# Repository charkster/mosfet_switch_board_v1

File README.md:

MOSFET Switch board which can quickly toggle the switch and then toggle GPIO pins by a programmable delay.

An Adafruit QT PY SAMD21 UF2 file is included. See test_mosfet_switch_board.py for SCPI commands.

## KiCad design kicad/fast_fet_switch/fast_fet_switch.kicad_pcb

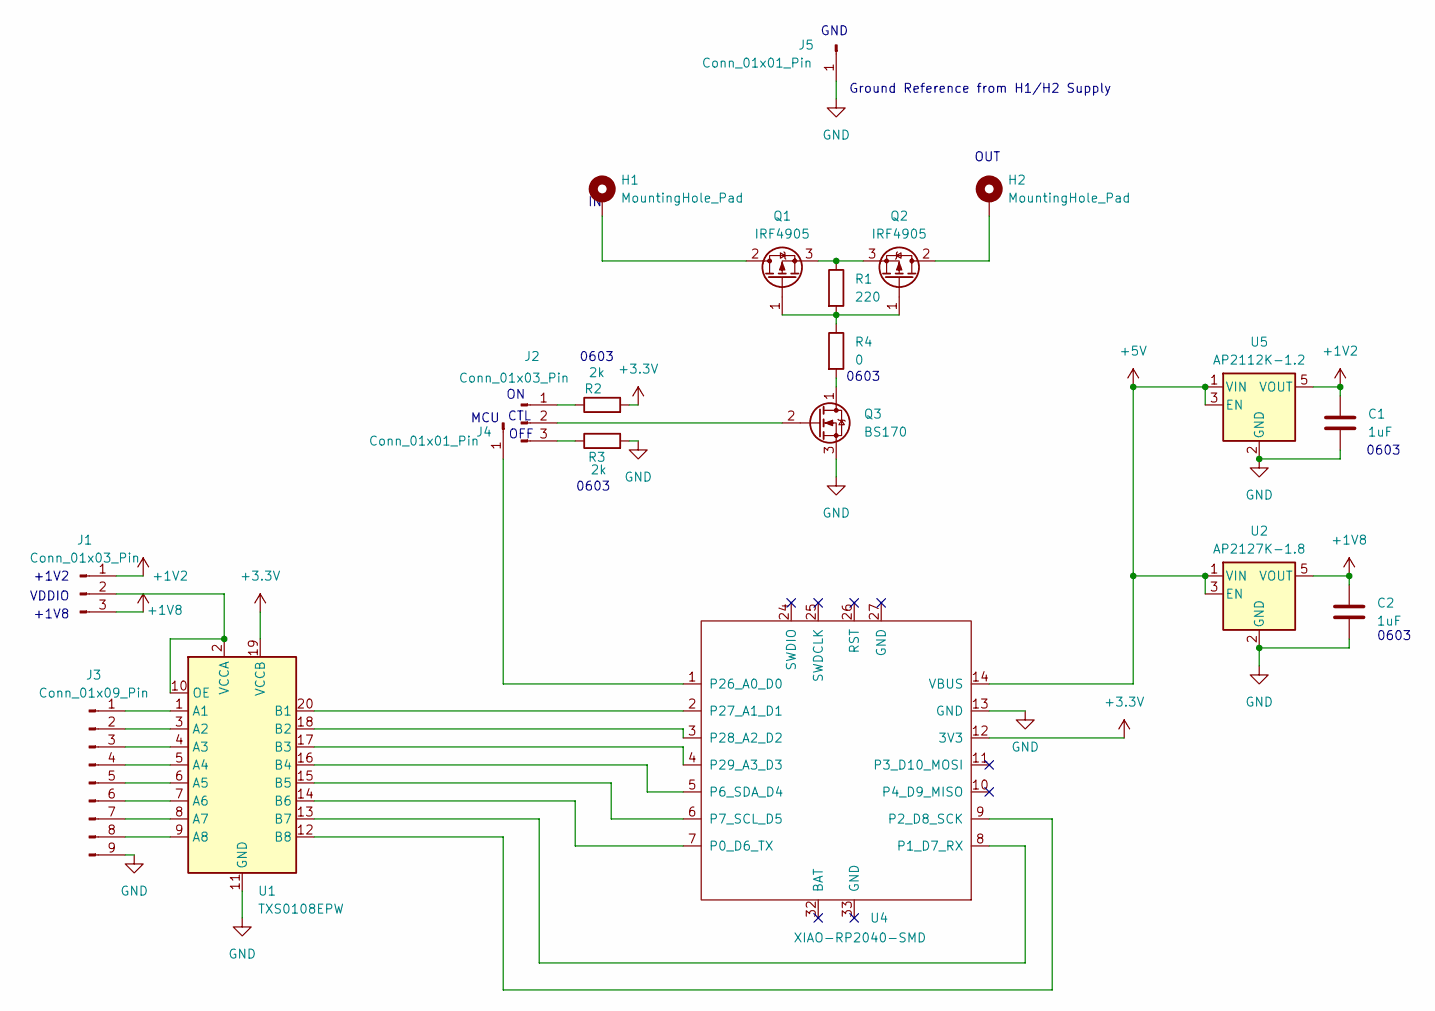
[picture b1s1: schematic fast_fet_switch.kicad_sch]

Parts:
C1, C2: 1uF; C_0603_1608Metric
H1, H2: MountingHole_Pad; MountingHole_6.4mm_M6_ISO7380_Pad_TopBottom
J1, J2: Conn_01x03_Pin; PinHeader_1x03_P2.54mm_Vertical
J3: Conn_01x09_Pin; PinHeader_1x09_P2.54mm_Vertical
J4, J5: Conn_01x01_Pin; PinHeader_1x01_P2.54mm_Vertical
Q1, Q2: IRF4905; TO-220-3_Vertical
Q3: BS170; TO-92_Inline
R1: 220; R_0603_1608Metric
R2, R3: 2k; R_0603_1608Metric
R4: 0; R_0603_1608Metric
U1: TXS0108EPW; TSSOP-20_4.4x6.5mm_P0.65mm
U2: AP2127K-1.8; SOT-23-5
U4: XIAO-RP2040-SMD
U5: AP2112K-1.2; SOT-23-5

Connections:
+1V2: C1.1, J1.1, U5.5 (VOUT)
+1V8: C2.1, J1.3, U2.5 (VOUT)
+3.3V: R2.2, U1.19 (VCCB), U4.12 (3V3)
+5V: U2.1 (VIN), U2.3 (EN), U4.14 (VBUS), U5.1 (VIN), U5.3 (EN)
GND: C1.2, C2.2, J3.9, J5.1 (Pin_1_1), Q3.3 (S), R3.2, U1.11 (GND), U2.2 (GND), U4.13 (GND), U5.2 (GND)
unnamed: J1.2, U1.2 (VCCA), U1.10 (OE)
unnamed: J2.1, R2.1
unnamed: J2.2, Q3.2 (G)
unnamed: J2.3, R3.1
unnamed: J3.1, U1.1 (A1)
unnamed: J3.2, U1.3 (A2)
unnamed: J3.3, U1.4 (A3)
unnamed: J3.4, U1.5 (A4)
unnamed: J3.5, U1.6 (A5)
unnamed: J3.6, U1.7 (A6)
unnamed: J3.7, U1.8 (A7)
unnamed: J3.8, U1.9 (A8)
unnamed: J4.1 (Pin_1_1), U4.1 (P26_A0_D0)
unnamed: H1.1 (1_1), Q1.2 (D)
unnamed: Q1.1 (G), Q2.1 (G), R1.2, R4.1
unnamed: Q1.3 (S), Q2.3 (S), R1.1
unnamed: H2.1 (1_1), Q2.2 (D)
unnamed: Q3.1 (D), R4.2
unnamed: U1.20 (B1), U4.2 (P27_A1_D1)
unnamed: U1.18 (B2), U4.3 (P28_A2_D2)
unnamed: U1.17 (B3), U4.4 (P29_A3_D3)
unnamed: U1.16 (B4), U4.5 (P6_SDA_D4)
unnamed: U1.15 (B5), U4.6 (P7_SCL_D5)
unnamed: U1.14 (B6), U4.7 (P0_D6_TX)
unnamed: U1.13 (B7), U4.8 (P1_D7_RX)
unnamed: U1.12 (B8), U4.9 (P2_D8_SCK)

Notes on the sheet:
+1V2
VDDIO
MCU
0603
OFF
OUT
Ground Reference from H1/H2 Supply
GND
CTL
+1V8

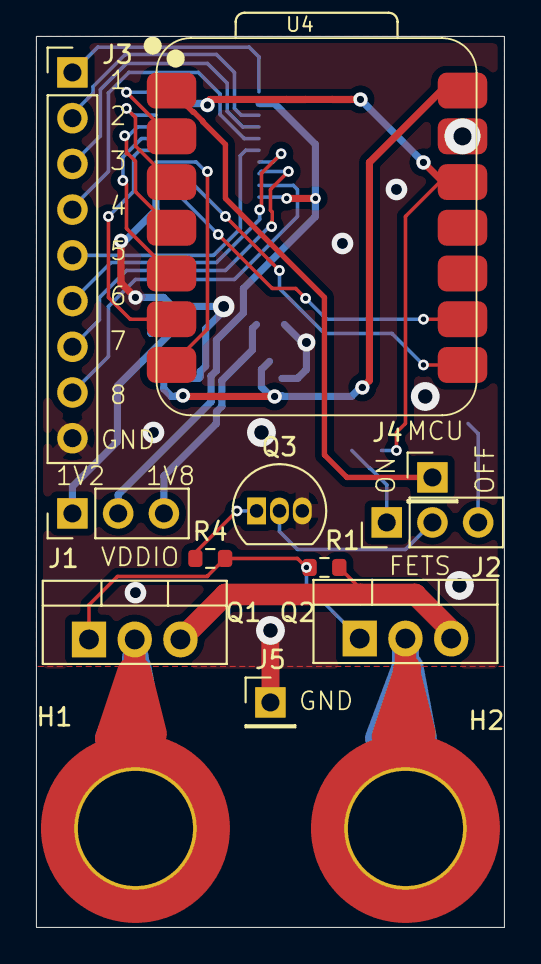
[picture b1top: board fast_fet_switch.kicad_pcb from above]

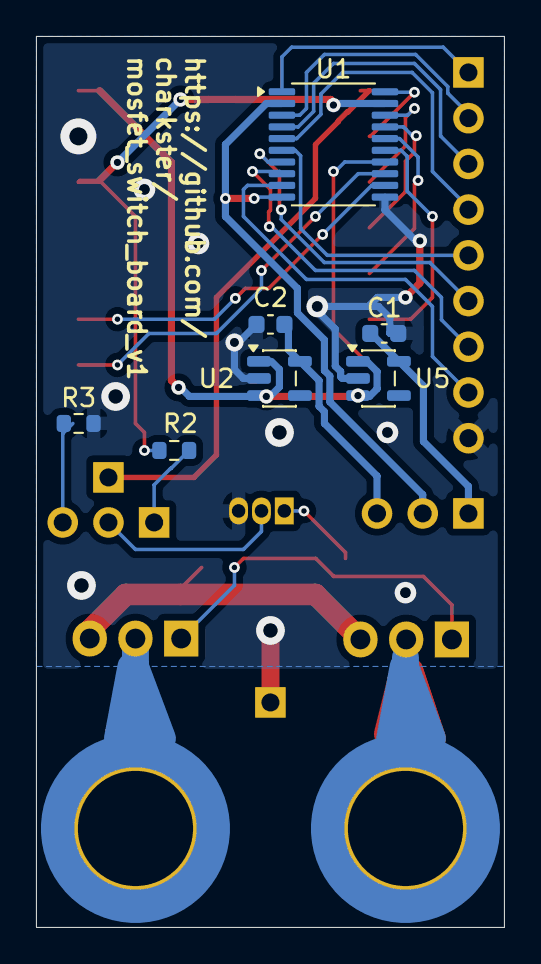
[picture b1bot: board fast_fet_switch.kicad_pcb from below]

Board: 2 copper layers, 26.0 x 49.5 mm, 20 parts (7 on the bottom side), 31 nets.

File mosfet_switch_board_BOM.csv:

Reference,Qty,Value,Footprint,Datasheet
"C1,C2",2,1uF,Capacitor_SMD:C_0603_1608Metric,
"J1,J2",2,Conn_01x03_Pin,Connector_PinHeader_2.54mm:PinHeader_1x03_P2.54mm_Vertical,
J3,1,Conn_01x09_Pin,Connector_PinHeader_2.54mm:PinHeader_1x09_P2.54mm_Vertical,
"J4,J5",2,Conn_01x01_Pin,Connector_PinHeader_2.54mm:PinHeader_1x01_P2.54mm_Vertical,
"Q1,Q2",2,IRF4905,Package_TO_SOT_THT:TO-220-3_Vertical,http://www.infineon.com/dgdl/irf4905.pdf?fileId=5546d4625336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
Q3,1,BS170,Package_TO_SOT_THT:TO-92_Inline,https://www.onsemi.com/pub/Collateral/BS170-D.PDF
R1,1,220,Resistor_SMD:R_0603_1608Metric,
"R2,R3",2,2k,Resistor_SMD:R_0603_1608Metric,
R4,1,0,Resistor_SMD:R_0603_1608Metric,
U1,1,TXS0108EPW,Package_SO:TSSOP-20_4.4x6.5mm_P0.65mm,www.ti.com/lit/ds/symlink/txs0108e.pdf
U2,1,AP2127K-1.8,Package_TO_SOT_SMD:SOT-23-5,https://www.diodes.com/assets/Datasheets/AP2127.pdf
U4,1,QTPY-SAMD21-SMD,Library:QTPY-SAMD21-SMD,https://www.adafruit.com/product/4600
U5,1,AP2112K-1.2,Package_TO_SOT_SMD:SOT-23-5,https://www.diodes.com/assets/Datasheets/AP2112.pdf
